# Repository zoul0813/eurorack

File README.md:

# Projects

- Clock Divider (QT Py)
- LFO (Nano)
- 2OSC VCO (Nano)
- Additive VCO (Nano)
- Chord VCO (Nano)
- FM VCO (Nano)
- Additive VCO (QT Py)
- Chord VCO (QT Py)
- FM VCO (QT Py)
- 6CH Euclidean Gate Sequencer (Nano)

## Current Dev Boards

- Arduino Nano
- Adafruit QT Py

#### Possible Dev Boards
- Adafruit Feather M0
- Adafruit Feather M4
- Seeeduino Xia
- STM32 Nucleo G031k8
- STM32 Nucleo G071RB

### Licenses, References, and other credits

A large number of these projects are based on, or inspired by [Hagiwo on YouTube](https://www.youtube.com/c/HAGIWO) with schematics found on (note.com/solder_state)[https://note.com/solder_state].

Some or all of the code provided by Hagiwo has been updated.

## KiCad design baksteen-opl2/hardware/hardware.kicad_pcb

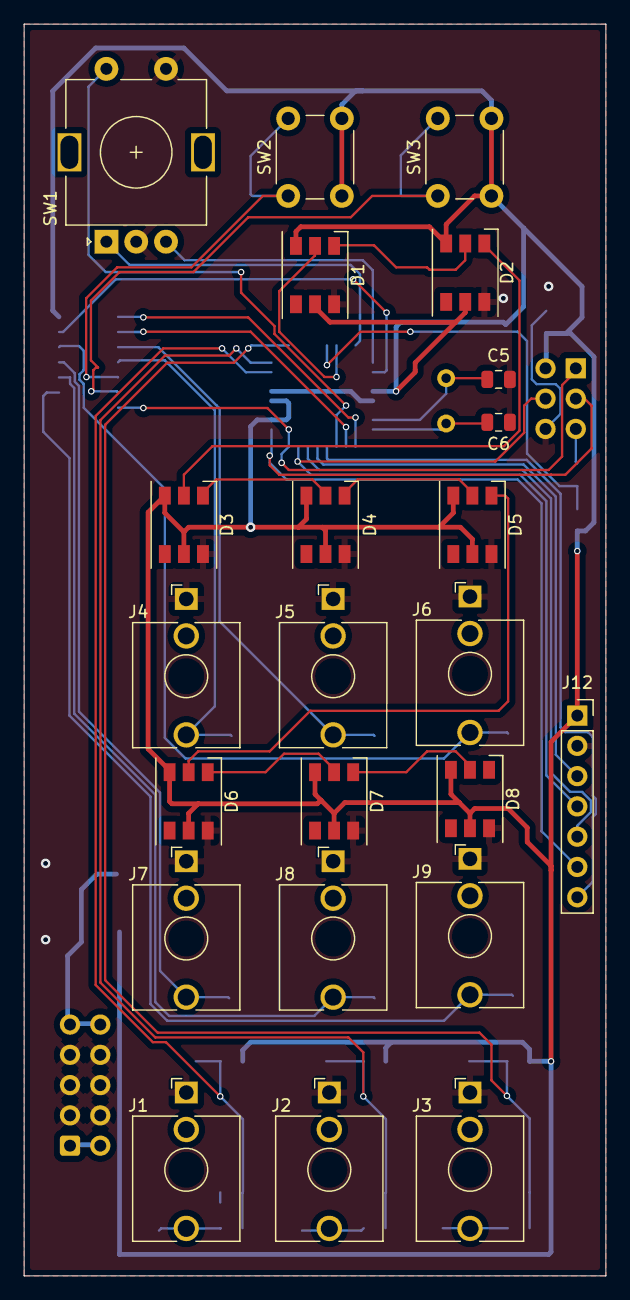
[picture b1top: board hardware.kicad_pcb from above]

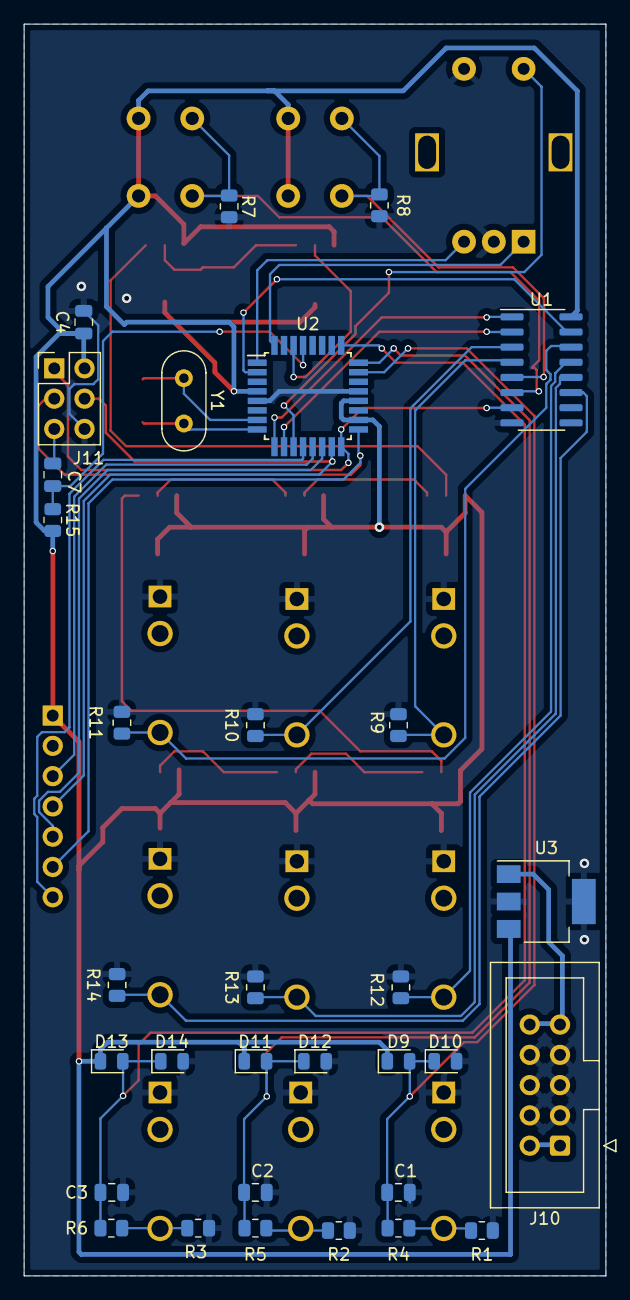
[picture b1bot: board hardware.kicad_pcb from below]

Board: 2 copper layers, 48.8 x 105.0 mm, 55 parts (32 on the bottom side), 42 nets.

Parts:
C1, C2, C3: 68nF; C_0805_2012Metric
C4, C7: 100nF; C_0805_2012Metric
C5, C6: 22pF; C_0805_2012Metric
D1, D2, D3, D4, D5, D6, D7, D8: WS2812; LED_WS2812_PLCC6_5.0x5.0mm_P1.6mm
D9, D10, D11, D12, D13, D14: BAT43; D_0805_2012Metric
J1: V/OCT; Jack_3.5mm_QingPu_WQP-PJ398SM_Vertical_CircularHoles
J2: CV1; Jack_3.5mm_QingPu_WQP-PJ398SM_Vertical_CircularHoles
J3: CV2; Jack_3.5mm_QingPu_WQP-PJ398SM_Vertical_CircularHoles
J4: GATE1; Jack_3.5mm_QingPu_WQP-PJ398SM_Vertical_CircularHoles
J5: GATE2; Jack_3.5mm_QingPu_WQP-PJ398SM_Vertical_CircularHoles
J6: GATE3; Jack_3.5mm_QingPu_WQP-PJ398SM_Vertical_CircularHoles
J7: GATE4; Jack_3.5mm_QingPu_WQP-PJ398SM_Vertical_CircularHoles
J8: GATE5; Jack_3.5mm_QingPu_WQP-PJ398SM_Vertical_CircularHoles
J9: GATE6; Jack_3.5mm_QingPu_WQP-PJ398SM_Vertical_CircularHoles
J10: Eurorack Power; IDC-Header_2x05_P2.54mm_Vertical
J11: ICSP; PinHeader_2x03_P2.54mm_Vertical
J12: OPL; PinSocket_1x07_P2.54mm_Vertical
R1, R2, R3: 100k; R_0805_2012Metric
R4, R5, R6: 100; R_0805_2012Metric
R7, R8, R9, R10, R11, R12, R13, R14, R15: 10k; R_0805_2012Metric
SW1: Encoder; RotaryEncoder_Alps_EC11E-Switch_Vertical_H20mm
SW2, SW3: SW_Push; SW_PUSH_6mm_H5mm
U1: 74HC165; SOIC-16_3.9x9.9mm_P1.27mm
U2: ATmega328PB-A; TQFP-32_7x7mm_P0.8mm
U3: LM7805_TO220; SOT-223-3_TabPin2
Y1: 16Mhz; Crystal_HC52-6mm_Vertical

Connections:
5V: C4.1, D1.3 (VCC), D1.5 (VDD), D2.3 (VCC), D2.5 (VDD), D3.3 (VCC), D3.5 (VDD), D4.3 (VCC), D4.5 (VDD), D5.3 (VCC), D5.5 (VDD), D6.3 (VCC), D6.5 (VDD), D7.3 (VCC), D7.5 (VDD), D8.3 (VCC), D8.5 (VDD), D9.1 (K), D11.1 (K), D13.1 (K), J11.2, J12.1, R15.2, SW2.2, SW3.2, U1.16 (VCC), U2.4 (VCC), U2.18 (AVCC), U2.20 (AREF), U3.3 (VO)
+12V: J10.9, J10.10, U3.1 (VI)
-12V: J10.1, J10.2
CV1: C2.1, D11.2 (A), D12.1 (K), R5.2, U2.24 (PC1)
CV2: C3.1, D13.2 (A), D14.1 (K), R6.2, U2.25 (PC2)
ENC_1: SW1.A, U2.32 (PD2)
ENC_2: SW1.B, U2.1 (PD3)
ENC_SW: SW1.S2, U2.11 (PD7)
GATE1: J4.T, R9.2, U1.4 (D5)
GATE2: J5.T, R10.2, U1.3 (D4)
GATE3: J6.T, R11.2, U1.14 (D3)
GATE4: J7.T, R12.2, U1.13 (D2)
GATE5: J8.T, R13.2, U1.12 (D1)
GATE6: J9.T, R14.2, U1.11 (D0)
GND: C1.2, C2.2, C3.2, C4.2, C5.2, C6.2, D1.6 (VSS), D2.6 (VSS), D3.6 (VSS), D4.6 (VSS), D5.6 (VSS), D6.6 (VSS), D7.6 (VSS), D8.6 (VSS), D10.2 (A), D12.2 (A), D14.2 (A), J1.S, J2.S, J3.S, J4.S, J5.S, J6.S, J7.S, J8.S, J9.S, J10.3, J10.4, J10.5, J10.6, J10.7, J10.8, J11.6, J12.2, R1.2, R2.2, R3.2, R7.1, R8.1, R9.1, R10.1, R11.1, R12.1, R13.1, R14.1, SW1.C, SW1.S1, U1.8 (GND), U2.5 (GND), U2.21 (GND), U3.2 (GND)
MISO: J11.1, U1.7 (~Q7), U2.16 (PB4)
MOSI: J11.4, J12.4, U2.15 (PB3)
unnamed: C5.1, U2.7 (XTAL1/PB6), Y1.2
unnamed: C6.1, U2.8 (XTAL2/PB7), Y1.1
unnamed: C7.1, R15.1, U2.29 (~RESET/PC6)
unnamed: D1.1 (DOUT), D2.2 (DIN)
unnamed: D2.1 (DOUT), D3.2 (DIN)
unnamed: D4.1 (DOUT), D5.2 (DIN)
unnamed: D3.1 (DOUT), D4.2 (DIN)
unnamed: D5.1 (DOUT), D6.2 (DIN)
unnamed: D6.1 (DOUT), D7.2 (DIN)
unnamed: D7.1 (DOUT), D8.2 (DIN)
unnamed: J1.T, R1.1, R4.1
unnamed: J2.T, R2.1, R5.1
unnamed: J3.T, R3.1, R6.1
Next: R7.2, SW3.1, U1.6 (D7)
OPL_A0: J12.3, U2.13 (PB1)
OPL_LATCH: J12.5, U2.14 (PB2)
OPL_RESET: J12.7, U2.12 (PB0)
OPL_SHIFT: J11.3, J12.6, U2.17 (PB5)
PIXELS: D1.2 (DIN), U2.30 (PD0)
Prev: R8.2, SW2.1, U1.5 (D6)
RESET: C7.2, J11.5
SHIFT_CLK: U1.2 (CP), U2.10 (PD6)
SHIFT_CLKIN: U1.15 (~CE), U2.2 (PD4)
SHIFT_LOAD: U1.1 (~PL), U2.9 (PD5)
V/OCT: C1.1, D9.2 (A), D10.1 (K), R4.2, U2.23 (PC0)

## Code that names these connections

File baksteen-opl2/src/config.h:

#include <RotaryEncoder.h>

#ifndef __CONFIG_H
#define __CONFIG_H

#define DEBUG 0
#define DEBUG_VERBOSE 0
#define VERSION "0.0.5-alpha"
#define CV_VOCT A0
#define CV_CV1 A1
#define CV_CV2 A2
// #define CV_GATE 12

// 74hc165 pins       Nano                  | 74hc165
#define SHIFT_CLKIN 4 // Clock Inhibit  | 15
#define SHIFT_LOAD 5  // Shift/Load     | 1
#define SHIFT_CLK 6   // Clock          | 2
#define SHIFT_DATA 12 // Data / Qh      | 7

// bits for the 74hc165 values
#define CV_NEXT 0
#define CV_PREV 1
#define CV_GATE1 2
#define CV_GATE2 3
#define CV_GATE3 4
#define CV_GATE4 5
#define CV_GATE5 6
#define CV_GATE6 7

// #define B_PRESET_NEXT 5
// #define B_PRESET_PREV 6

#define ENCODER_1 2
#define ENCODER_2 3
#define ENCODER_SW 7
#define ENCODER_LATCH RotaryEncoder::LatchMode::FOUR3

#define VOICES 6

#define MODE_POLY 0
#define MODE_RHYTHM 1
#define MODE_CHORD 2
#define MODE_DEFAULT MODE_RHYTHM

#define NEOPIXEL_PIN 0 // On Trinket or Gemma, suggest changing this to 1
#define NEOPIXEL_NUM 8 // Popular NeoPixel ring size

#define NEOPIXEL_RHYTHM pixels.Color(244, 27, 63) // pink
#define NEOPIXEL_POLY pixels.Color(27,244,63) // green?
#define NEOPIXEL_CHORD pixels.Color(27,63,244) // blue?

#endif

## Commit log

2022-04-08 added .gitignore for PIO
2022-04-08 initial commit of early projects
2022-04-08 updated READ, VS Code workspace, project names
2022-04-08 renamed README.md
2022-04-12 added baksteen-opl2 with Arduino OPL2 Drum example reconfigured to work with solderstate-euclidean
2022-04-18 fixing submodule issues
2022-04-24 OPL2 with CV Input, using Hagiwo V/OCT into A1
2022-04-24 added preset next/prev via D3 and D4 with INPUT_PULLUP via Bounce2
2022-04-24 added Rotary Encoder w/ Switch, swapped D3,D4 for D5, D6, D2-3 are encoder, D7 is encoder switch
2022-04-25 added encoder options for ADSR
2022-04-25 added CV Gate to D12, over 10k pull down
2022-04-25 removed bounce delay on gate, now triggers whenever the gate goes high after going low
2022-04-25 'better' reads of the voct, by delaying for 16 loops before triggering the OPL
2022-04-30 added sn76489
2022-04-30 added schematic for SN76489 direct connect
2022-04-30 removed fg-info-cache
2022-04-30 updated to add v/oct resistors/caps
2022-05-01 added detune, noise and sweep pots
2022-05-05 added OPL schematic
2022-05-05 rearranged code into separate files
2022-05-06 added Poly Mode and Rhythm Mode support
2022-05-08 added power symbols, and NC to schematic
2022-05-08 added CHORD mode option, first Neopixel set as mode indicator, simple change mode with encoder push
2022-05-09 added chord mode with third/fifth
2022-05-14 updated schematic to include CV components, laid out components on PCB ... no traces run yet
2022-05-14 added debugging back in, adjusted pin assignments to match schematic
2022-05-14 removed nano, going with bare atmega328p in tqfp package
2022-05-15 added tracks ... mostly
2022-05-15 reran tracks ... mostly complete, couple DRC errors
